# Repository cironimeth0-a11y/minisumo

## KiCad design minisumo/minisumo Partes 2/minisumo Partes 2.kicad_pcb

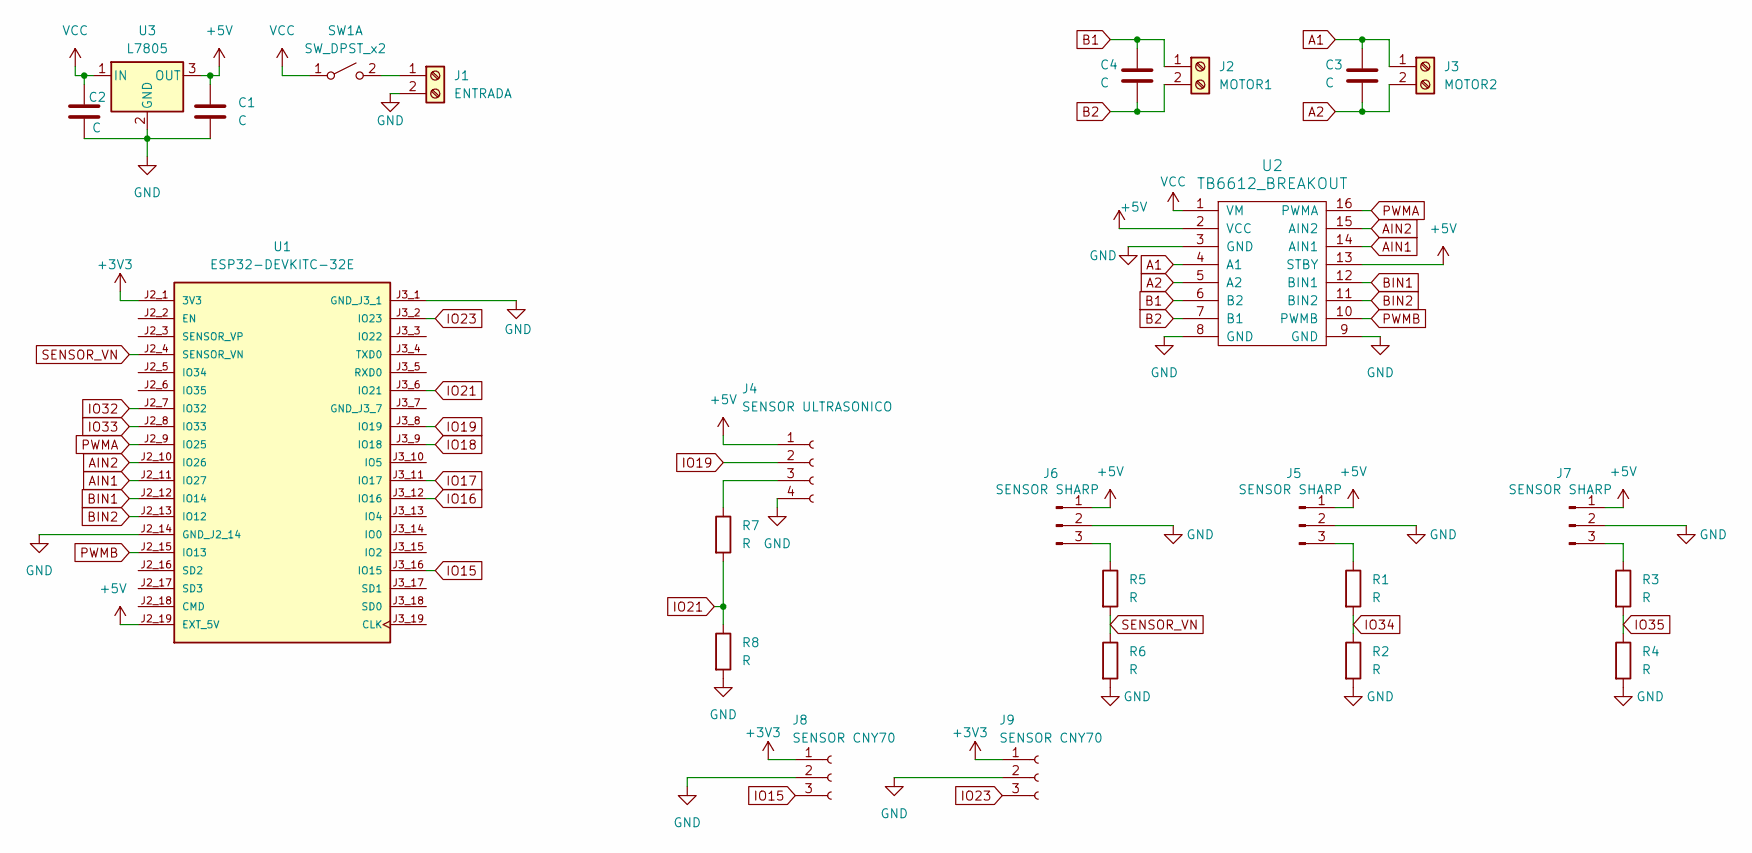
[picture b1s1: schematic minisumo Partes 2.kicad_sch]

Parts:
C1, C2, C3, C4: C; C_0805_2012Metric
J1: ENTRADA; BORNERA2
J2: MOTOR1; BORNERA2
J3: MOTOR2; BORNERA2
J4: SENSOR ULTRASONICO; pin_strip_4
J5, J6, J7: SENSOR SHARP; Pin_Header_3
J8, J9: SENSOR CNY70; Pin_Header_3
R1, R2, R3, R4, R5, R6, R7, R8: R; R_0805_2012Metric
SW1: SW_DPST_x2; SW_PUSH_1P1T_6x3.5mm_H4.3_APEM_MJTP1243
U1: ESP32-DEVKITC-32E; MODULE_ESP32-DEVKITC-32E; PARTREV 1.4
U2: TB6612_BREAKOUT; TB6612_Breakout
U3: L7805; to220

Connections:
+3V3: J8.1, J9.1, U1.J2_1 (3V3); also elsewhere on the board
+5V: C1.1, J4.1, J5.1, J6.1, J7.1, U1.J2_19 (EXT_5V), U2.2 (VCC), U2.13 (STBY), U3.3 (OUT); also elsewhere on the board
A1: C3.1, J3.1, U2.4 (A1)
A2: C3.2, J3.2, U2.5 (A2)
AIN1: U1.J2_11 (IO27), U2.14 (AIN1); also elsewhere on the board
AIN2: U1.J2_10 (IO26), U2.15 (AIN2); also elsewhere on the board
B1: C4.1, J2.1, U2.6 (B2)
B2: C4.2, J2.2, U2.7 (B1)
BIN1: U1.J2_12 (IO14), U2.12 (BIN1); also elsewhere on the board
BIN2: U1.J2_13 (IO12), U2.11 (BIN2); also elsewhere on the board
D2: J4.2, U1.J3_8 (IO19); also elsewhere on the board
D4: J8.3, U1.J3_16 (IO15); also elsewhere on the board
D15: J9.3, U1.J3_2 (IO23); also elsewhere on the board
D18: R7.2, R8.1, U1.J3_6 (IO21); also elsewhere on the board
D21: R3.2, R4.1; also elsewhere on the board
D27: R1.2, R2.1; also elsewhere on the board
GND: C1.2, C2.2, J1.2, J4.4, J5.2, J6.2, J7.2, J8.2, J9.2, R2.2, R4.2, R6.2, R8.2, U1.J2_14 (GND_J2_14), U1.J3_1 (GND_J3_1), U2.3 (GND), U2.8 (GND), U2.9 (GND), U3.2 (GND); also elsewhere on the board
unnamed: J1.1, SW1.2 (B)
unnamed: J4.3, R7.1
unnamed: J5.3, R1.1
unnamed: J6.3, R5.1
unnamed: J7.3, R3.1
PWMA: U1.J2_9 (IO25), U2.16 (PWMA); also elsewhere on the board
PWMB: U1.J2_15 (IO13), U2.10 (PWMB); also elsewhere on the board
VCC: C2.1, SW1.1 (A), U2.1 (VM), U3.1 (IN)
VN: R5.2, R6.1, U1.J2_4 (SENSOR_VN); also elsewhere on the board

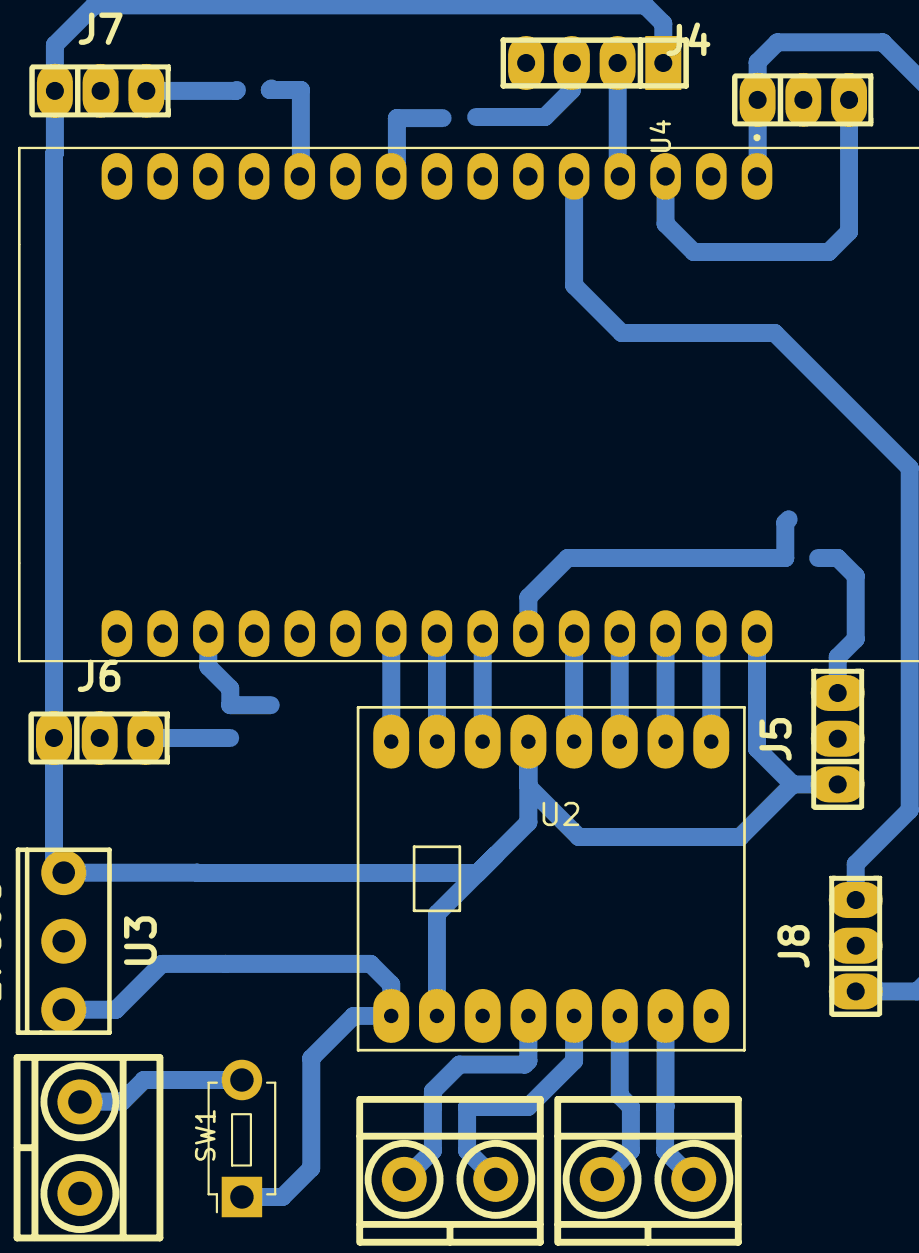
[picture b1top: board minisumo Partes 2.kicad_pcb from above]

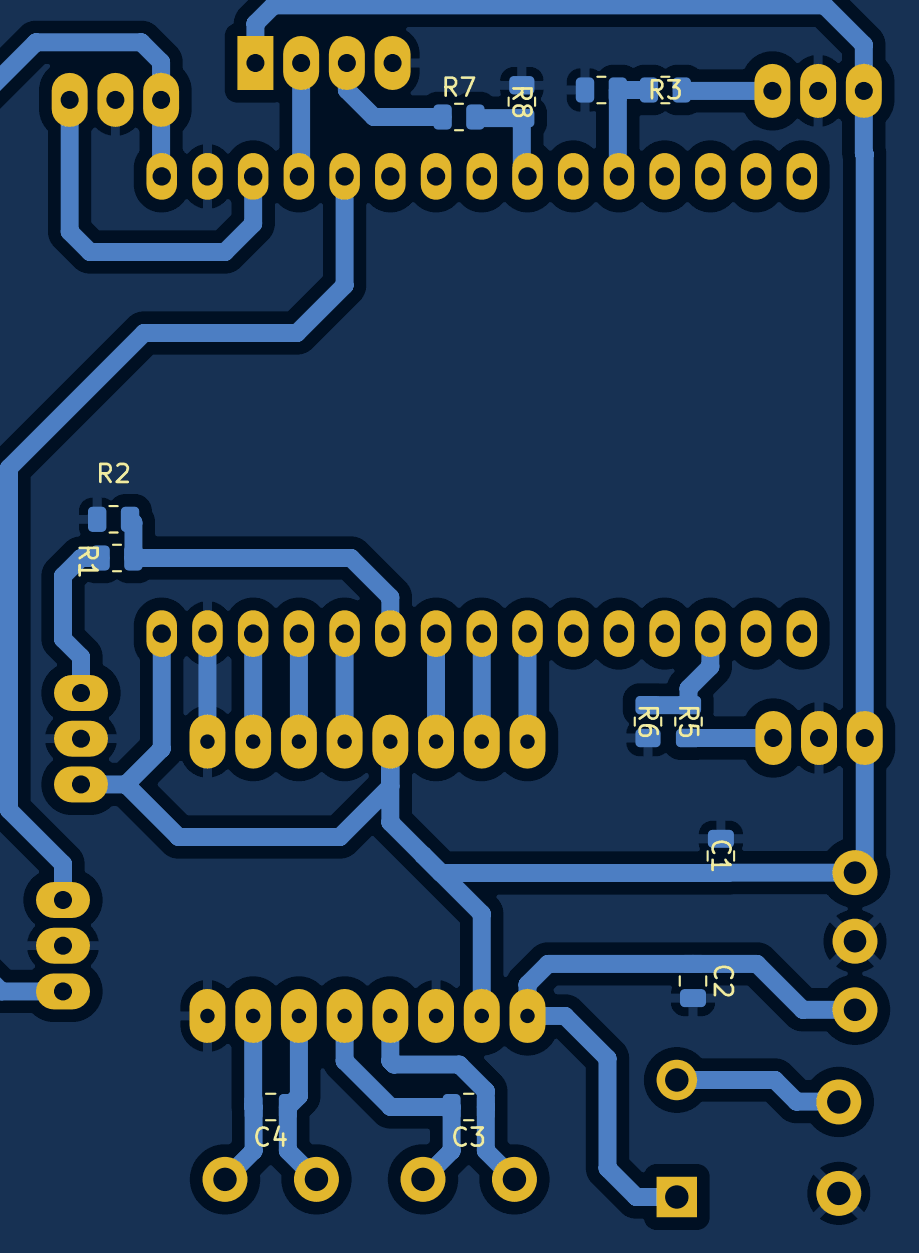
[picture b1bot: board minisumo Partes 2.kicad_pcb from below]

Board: 2 copper layers, 25 parts (12 on the bottom side), 26 nets.

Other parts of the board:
U4: ESP32-DEVKIT-V1; MODULE_ESP32_DEVKIT_V1

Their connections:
+3V3: U4.1 (3V3); also elsewhere on the board
+5V: U4.30 (VIN); also elsewhere on the board
AIN1: U4.24 (D26); also elsewhere on the board
AIN2: U4.23 (D25); also elsewhere on the board
BIN1: U4.26 (D14); also elsewhere on the board
BIN2: U4.27 (D12); also elsewhere on the board
D2: U4.4 (D2); also elsewhere on the board
D4: U4.5 (D4); also elsewhere on the board
D15: U4.3 (D15); also elsewhere on the board
D18: U4.9 (D18); also elsewhere on the board
D21: U4.11 (D21); also elsewhere on the board
D27: U4.25 (D27); also elsewhere on the board
GND: U4.2 (GND), U4.29 (GND); also elsewhere on the board
PWMA: U4.22 (D33); also elsewhere on the board
PWMB: U4.28 (D13); also elsewhere on the board
VN: U4.18 (VN); also elsewhere on the board

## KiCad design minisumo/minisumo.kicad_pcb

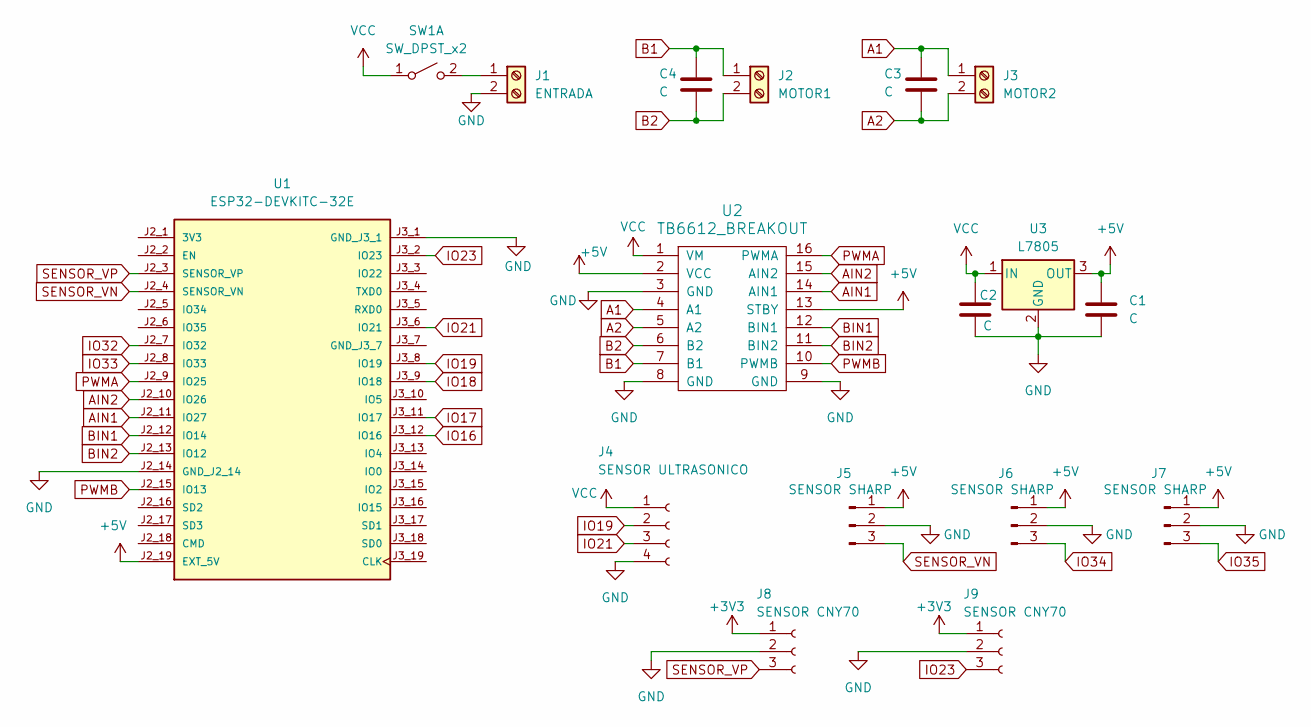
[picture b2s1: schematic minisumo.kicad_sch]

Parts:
C1, C2, C3, C4: C; CAP_0.2
J1: ENTRADA; BORNERA2
J2: MOTOR1; BORNERA2
J3: MOTOR2; BORNERA2
J4: SENSOR ULTRASONICO; pin_strip_4
J5, J6, J7: SENSOR SHARP; Pin_Header_3
J8, J9: SENSOR CNY70; Pin_Header_3
SW1: SW_DPST_x2; SW_PUSH_1P1T_6x3.5mm_H4.3_APEM_MJTP1243
U1: ESP32-DEVKITC-32E; MODULE_ESP32-DEVKITC-32E; PARTREV 1.4
U2: TB6612_BREAKOUT; TB6612_Breakout
U3: L7805; to220

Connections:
+3V3: J8.1, J9.1
+5V: C1.1, J5.1, J6.1, J7.1, U1.J2_19 (EXT_5V), U2.2 (VCC), U2.13 (STBY), U3.3 (OUT)
A1: C3.1, J3.1, U2.4 (A1)
A2: C3.2, J3.2, U2.5 (A2)
AIN1: U1.J2_11 (IO27), U2.14 (AIN1)
AIN2: U1.J2_10 (IO26), U2.15 (AIN2)
B1: C4.1, J2.1, U2.7 (B1)
B2: C4.2, J2.2, U2.6 (B2)
BIN1: U1.J2_12 (IO14), U2.12 (BIN1)
BIN2: U1.J2_13 (IO12), U2.11 (BIN2)
GND: C1.2, C2.2, J1.2, J4.4, J5.2, J6.2, J7.2, J8.2, J9.2, U1.J2_14 (GND_J2_14), U1.J3_1 (GND_J3_1), U2.3 (GND), U2.8 (GND), U2.9 (GND), U3.2 (GND)
IO16: U1.J3_12 (IO16)
IO17: U1.J3_11 (IO17)
IO18: U1.J3_9 (IO18)
IO19: J4.2, U1.J3_8 (IO19)
IO21: J4.3, U1.J3_6 (IO21)
IO23: J9.3, U1.J3_2 (IO23)
IO32: U1.J2_7 (IO32)
IO33: U1.J2_8 (IO33)
IO34: J6.3
IO35: J7.3
unnamed: J1.1, SW1.2 (B)
PWMA: U1.J2_9 (IO25), U2.16 (PWMA)
PWMB: U1.J2_15 (IO13), U2.10 (PWMB)
SENSOR_VN: J5.3, U1.J2_4 (SENSOR_VN)
SENSOR_VP: J8.3, U1.J2_3 (SENSOR_VP)
VCC: C2.1, J4.1, SW1.1 (A), U2.1 (VM), U3.1 (IN)

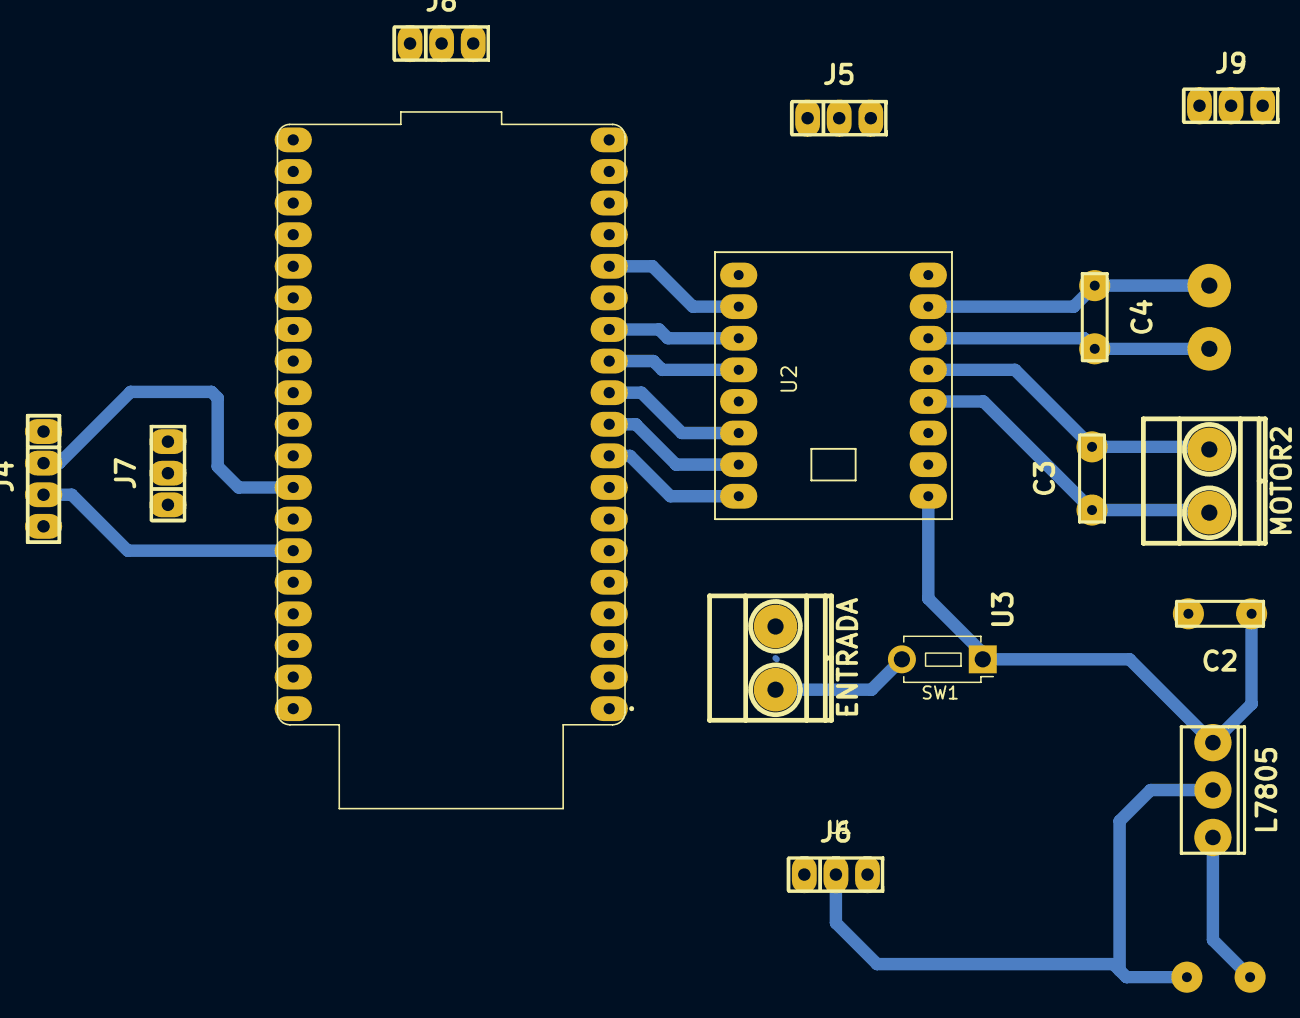
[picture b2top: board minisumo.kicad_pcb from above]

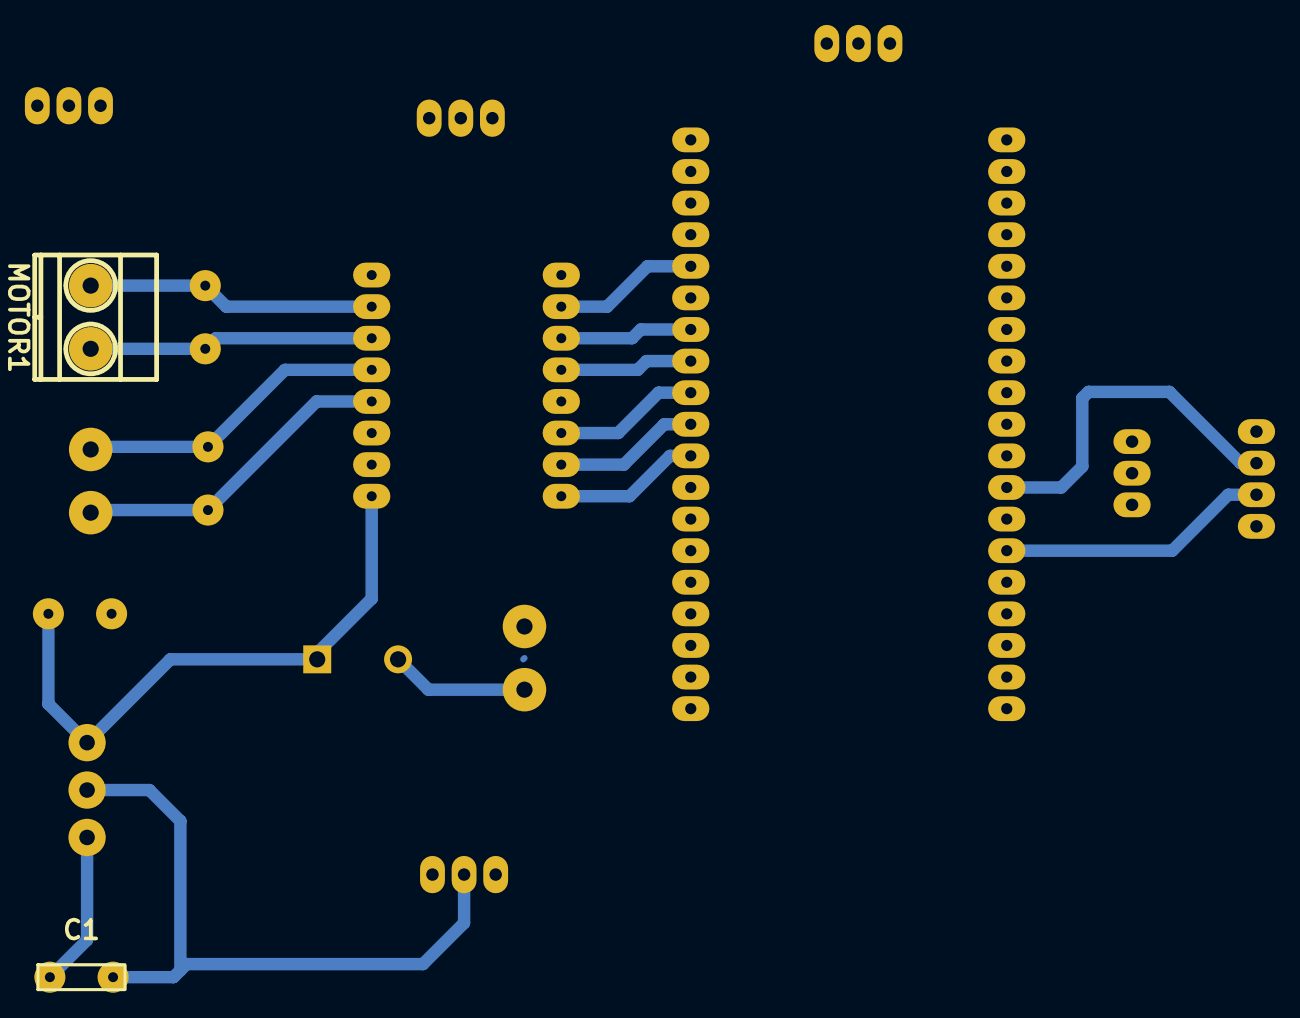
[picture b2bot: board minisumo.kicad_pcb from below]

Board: 2 copper layers, 17 parts (2 on the bottom side), 20 nets.

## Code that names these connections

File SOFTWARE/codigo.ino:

/*************************************************
   ROBOT ESP32 + TB6612 + HC-SR04 + CNY70 + SHARP
*************************************************/

// ========= TB6612 =========

// Motor A
#define PWMA 18
#define AIN1 16
#define AIN2 17

// Motor B
#define PWMB 5
#define BIN1 26
#define BIN2 25

// Standby
#define STBY 4


// ========= HC-SR04 =========

#define TRIG_PIN 21
#define ECHO_PIN 19


// ========= SENSORES SHARP =========

// Frente
#define SHARP_FRONT 39

// Izquierda
#define SHARP_LEFT 34

// Derecha
#define SHARP_RIGHT 35


// ========= SENSORES CNY70 =========

// Abajo
#define CNY70_DOWN 36

// Frente
#define CNY70_FRONT 23


// ========= PWM =========

#define PWM_FREQ 1000
#define PWM_RESOLUTION 8

#define CHANNEL_A 0
#define CHANNEL_B 1


// =====================================================
// SETUP
// =====================================================

void setup() {

  Serial.begin(115200);

  // ===== TB6612 =====
  pinMode(AIN1, OUTPUT);
  pinMode(AIN2, OUTPUT);

  pinMode(BIN1, OUTPUT);
  pinMode(BIN2, OUTPUT);

  pinMode(STBY, OUTPUT);

  digitalWrite(STBY, HIGH);

  // PWM
  ledcSetup(CHANNEL_A, PWM_FREQ, PWM_RESOLUTION);
  ledcAttachPin(PWMA, CHANNEL_A);

  ledcSetup(CHANNEL_B, PWM_FREQ, PWM_RESOLUTION);
  ledcAttachPin(PWMB, CHANNEL_B);

  // ===== HC-SR04 =====
  pinMode(TRIG_PIN, OUTPUT);
  pinMode(ECHO_PIN, INPUT);

  // ===== Sensores =====
  pinMode(CNY70_DOWN, INPUT);
  pinMode(CNY70_FRONT, INPUT);

  pinMode(SHARP_FRONT, INPUT);
  pinMode(SHARP_LEFT, INPUT);
  pinMode(SHARP_RIGHT, INPUT);

  Serial.println("Sistema iniciado");
}


// =====================================================
// LOOP
// =====================================================

void loop() {

  long distancia = medirDistancia();

  int sharpFront = analogRead(SHARP_FRONT);
  int sharpLeft  = analogRead(SHARP_LEFT);
  int sharpRight = analogRead(SHARP_RIGHT);

  int cnyDown  = analogRead(CNY70_DOWN);
  int cnyFront = analogRead(CNY70_FRONT);

  // ===== Mostrar datos =====
  Serial.println("==========");

  Serial.print("Ultrasonico: ");
  Serial.print(distancia);
  Serial.println(" cm");

  Serial.print("Sharp Frente: ");
  Serial.println(sharpFront);

  Serial.print("Sharp Izq: ");
  Serial.println(sharpLeft);

  Serial.print("Sharp Der: ");
  Serial.println(sharpRight);

  Serial.print("CNY70 Abajo: ");
  Serial.println(cnyDown);

  Serial.print("CNY70 Frente: ");
  Serial.println(cnyFront);


  // =================================================
  // LOGICA DEL ROBOT
  // =================================================

  // Si detecta obstáculo cerca
  if (distancia < 15 && distancia > 0) {

    detenerMotores();
    delay(300);

    retroceder(180);
    delay(500);

    girarDerecha(180);
    delay(500);
  }

  // Si el CNY70 de abajo detecta borde
  else if (cnyDown < 1500) {

    detenerMotores();
    delay(200);

    retroceder(180);
    delay(500);

    girarIzquierda(180);
    delay(500);
  }

  // Si sensor frontal detecta algo
  else if (sharpFront > 2500 || cnyFront > 2000) {

    detenerMotores();
    delay(200);

    girarDerecha(180);
    delay(400);
  }

  // Movimiento normal
  else {

    avanzar(180);
  }

  delay(50);
}


// =====================================================
// FUNCIONES MOTORES
// =====================================================

void avanzar(int velocidad) {

  digitalWrite(AIN1, HIGH);
  digitalWrite(AIN2, LOW);

  digitalWrite(BIN1, HIGH);
  digitalWrite(BIN2, LOW);

  ledcWrite(CHANNEL_A, velocidad);
  ledcWrite(CHANNEL_B, velocidad);
}

void retroceder(int velocidad) {

  digitalWrite(AIN1, LOW);
  digitalWrite(AIN2, HIGH);

  digitalWrite(BIN1, LOW);
  digitalWrite(BIN2, HIGH);

  ledcWrite(CHANNEL_A, velocidad);
  ledcWrite(CHANNEL_B, velocidad);
}

void girarDerecha(int velocidad) {

  digitalWrite(AIN1, HIGH);
  digitalWrite(AIN2, LOW);

  digitalWrite(BIN1, LOW);
  digitalWrite(BIN2, HIGH);

  ledcWrite(CHANNEL_A, velocidad);
  ledcWrite(CHANNEL_B, velocidad);
}

void girarIzquierda(int velocidad) {

  digitalWrite(AIN1, LOW);
  digitalWrite(AIN2, HIGH);

  digitalWrite(BIN1, HIGH);
  digitalWrite(BIN2, LOW);

  ledcWrite(CHANNEL_A, velocidad);
  ledcWrite(CHANNEL_B, velocidad);
}

void detenerMotores() {

  ledcWrite(CHANNEL_A, 0);
  ledcWrite(CHANNEL_B, 0);
}


// =====================================================
// HC-SR04
// =====================================================

long medirDistancia() {

  digitalWrite(TRIG_PIN, LOW);
  delayMicroseconds(5);

  digitalWrite(TRIG_PIN, HIGH);
  delayMicroseconds(10);

  digitalWrite(TRIG_PIN, LOW);

  long duracion = pulseIn(ECHO_PIN, HIGH, 30000);

  long distancia = duracion * 0.034 / 2;

  return distancia;
}

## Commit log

2026-05-19 primer commit
2026-05-26 26/5/14
2026-06-16 16/6
